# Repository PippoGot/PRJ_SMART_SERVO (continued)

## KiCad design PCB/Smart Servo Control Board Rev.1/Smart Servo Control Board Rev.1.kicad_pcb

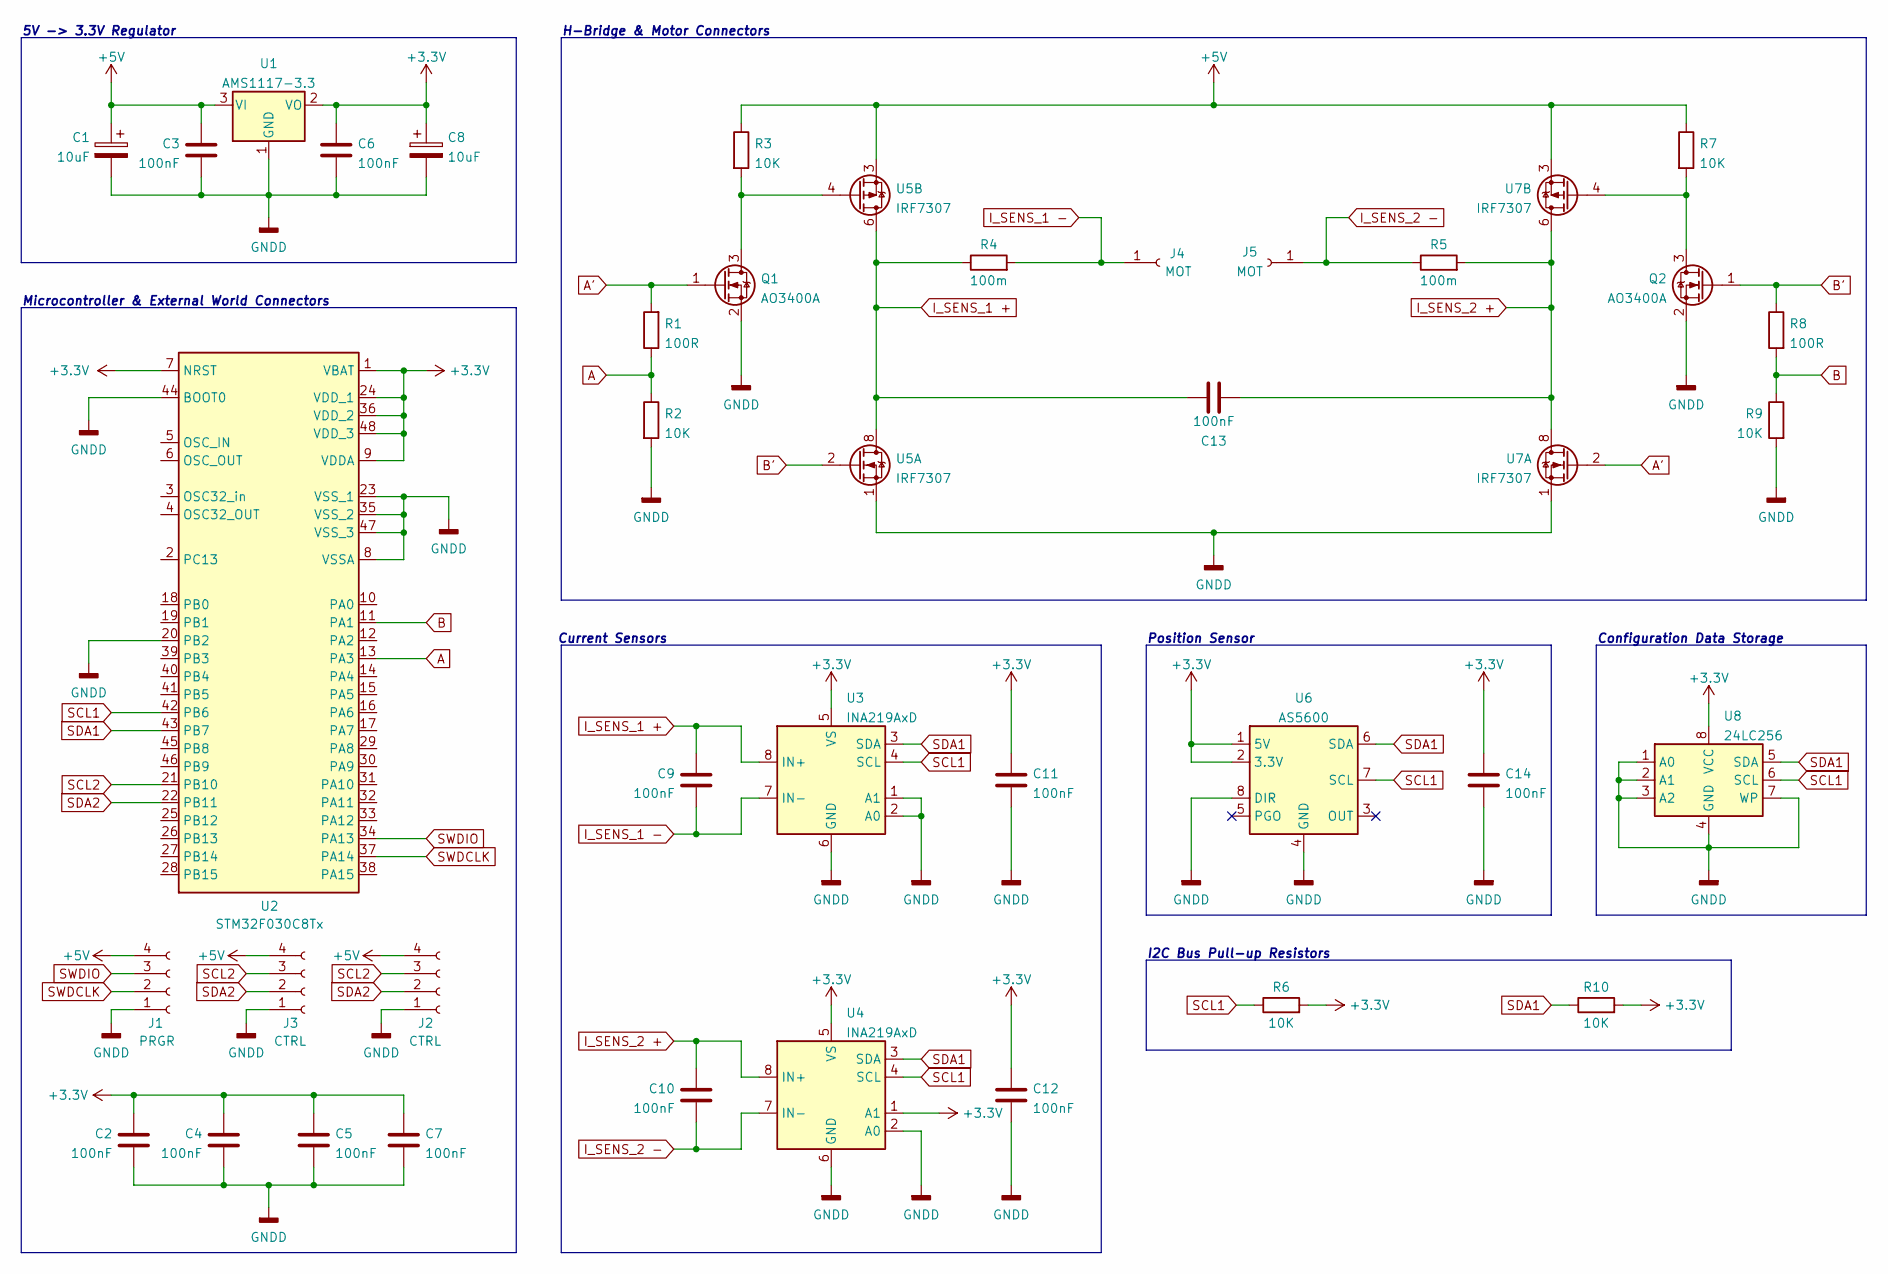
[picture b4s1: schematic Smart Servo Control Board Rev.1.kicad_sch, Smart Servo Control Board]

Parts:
C1, C8: 10uF; C_0603_1608Metric_Pad1.08x0.95mm_HandSolder
C2, C3, C4, C5, C6, C7, C9, C10, C11, C12, C13, C14: 100nF; C_0603_1608Metric_Pad1.08x0.95mm_HandSolder
J1: PRGR; PinSocket_1x04_P2.54mm_Vertical
J2, J3: CTRL; PinSocket_1x04_P2.54mm_Vertical
J4, J5: MOT; PinSocket_1x01_P2.54mm_Vertical
Q1, Q2: AO3400A; SOT-23
R1, R8: 100R; R_0603_1608Metric_Pad0.98x0.95mm_HandSolder
R2, R3, R6, R7, R9, R10: 10K; R_0603_1608Metric_Pad0.98x0.95mm_HandSolder
R4, R5: 100m; R_1206_3216Metric_Pad1.30x1.75mm_HandSolder
U1: AMS1117-3.3; SOT-223-3_TabPin2
U2: STM32F030C8Tx; LQFP-48_7x7mm_P0.5mm
U3, U4: INA219AxD; SOIC-8_3.9x4.9mm_P1.27mm
U5, U7: IRF7307; SOIC-8_3.9x4.9mm_P1.27mm
U6: AS5600; SOIC-8_3.9x4.9mm_P1.27mm
U8: 24LC256; SOIC-8_3.9x4.9mm_P1.27mm

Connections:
+3V3: C2.1, C4.1, C5.1, C6.1, C7.1, C8.1, C11.2, C12.2, C14.1, R6.2, R10.2, U1.2 (VO), U2.1 (VBAT), U2.7 (NRST), U2.9 (VDDA), U2.24 (VDD_1), U2.36 (VDD_2), U2.48 (VDD_3), U3.5 (VS), U4.1 (A1), U4.5 (VS), U6.1 (5V), U6.2 (3.3V), U8.8 (VCC)
+5V: C1.1, C3.1, J1.4, J2.4, J3.4, R3.1, R7.1, U1.3 (VI), U5.3, U7.3
A: R1.1, R2.1, U2.13 (PA3)
A': Q1.1 (G), R1.2, U7.2
B: R8.2, R9.1, U2.11 (PA1)
B': Q2.1 (G), R8.1, U5.2
GNDD: C1.2, C2.2, C3.2, C4.2, C5.2, C6.2, C7.2, C8.2, C11.1, C12.1, C14.2, J1.1, J2.1, J3.1, Q1.2 (S), Q2.2 (S), R2.2, R9.2, U1.1 (GND), U2.8 (VSSA), U2.20 (PB2), U2.23 (VSS_1), U2.35 (VSS_2), U2.44 (BOOT0), U2.47 (VSS_3), U3.1 (A1), U3.2 (A0), U3.6 (GND), U4.2 (A0), U4.6 (GND), U5.1, U6.4 (GND), U6.8 (DIR), U7.1, U8.1 (A0), U8.2 (A1), U8.3 (A2), U8.4 (GND), U8.7 (WP)
I_SENS_1 +: C9.1, C13.1, R4.1, U3.8 (IN+), U5.5, U5.6, U5.7, U5.8
I_SENS_1 -: C9.2, J4.1, R4.2, U3.7 (IN-)
I_SENS_2 +: C10.1, C13.2, R5.2, U4.8 (IN+), U7.5, U7.6, U7.7, U7.8
I_SENS_2 -: C10.2, J5.1, R5.1, U4.7 (IN-)
unnamed: Q1.3 (D), R3.2, U5.4
unnamed: Q2.3 (D), R7.2, U7.4
SCL1: R6.1, U2.42 (PB6), U3.4 (SCL), U4.4 (SCL), U6.7 (SCL), U8.6 (SCL)
SCL2: J2.3, J3.3, U2.21 (PB10)
SDA1: R10.1, U2.43 (PB7), U3.3 (SDA), U4.3 (SDA), U6.6 (SDA), U8.5 (SDA)
SDA2: J2.2, J3.2, U2.22 (PB11)
SWDCLK: J1.2, U2.37 (PA14)
SWDIO: J1.3, U2.34 (PA13)

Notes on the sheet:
Configuration Data Storage
Position Sensor
I2C Bus Pull-up Resistors
H-Bridge & Motor Connectors
5V -> 3.3V Regulator
Current Sensors
Microcontroller & External World Connectors

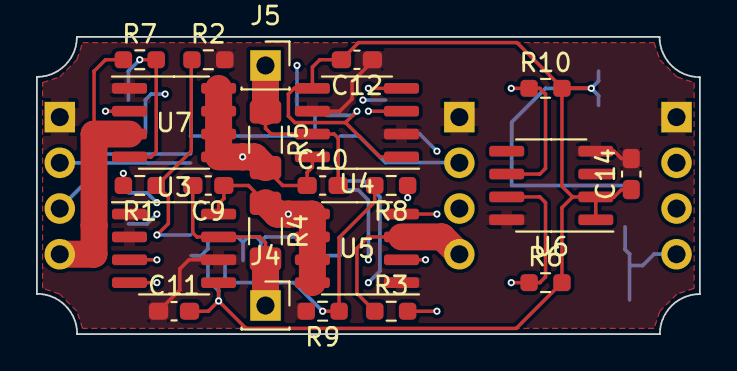
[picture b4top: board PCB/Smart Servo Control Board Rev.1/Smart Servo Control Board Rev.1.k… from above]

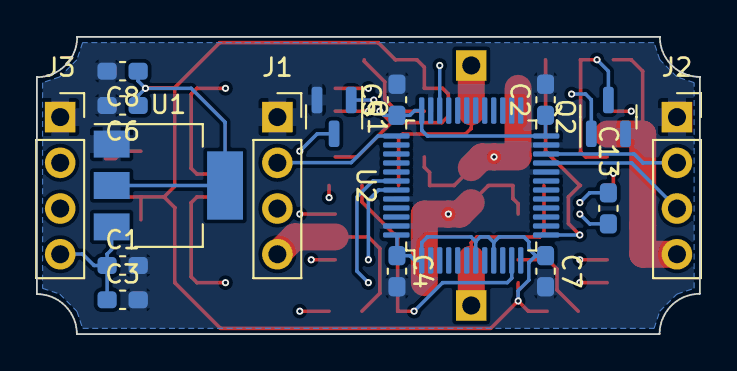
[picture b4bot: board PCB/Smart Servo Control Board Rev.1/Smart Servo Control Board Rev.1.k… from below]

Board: 4 copper layers, 36.8 x 16.5 mm, 38 parts (16 on the bottom side), 19 nets.

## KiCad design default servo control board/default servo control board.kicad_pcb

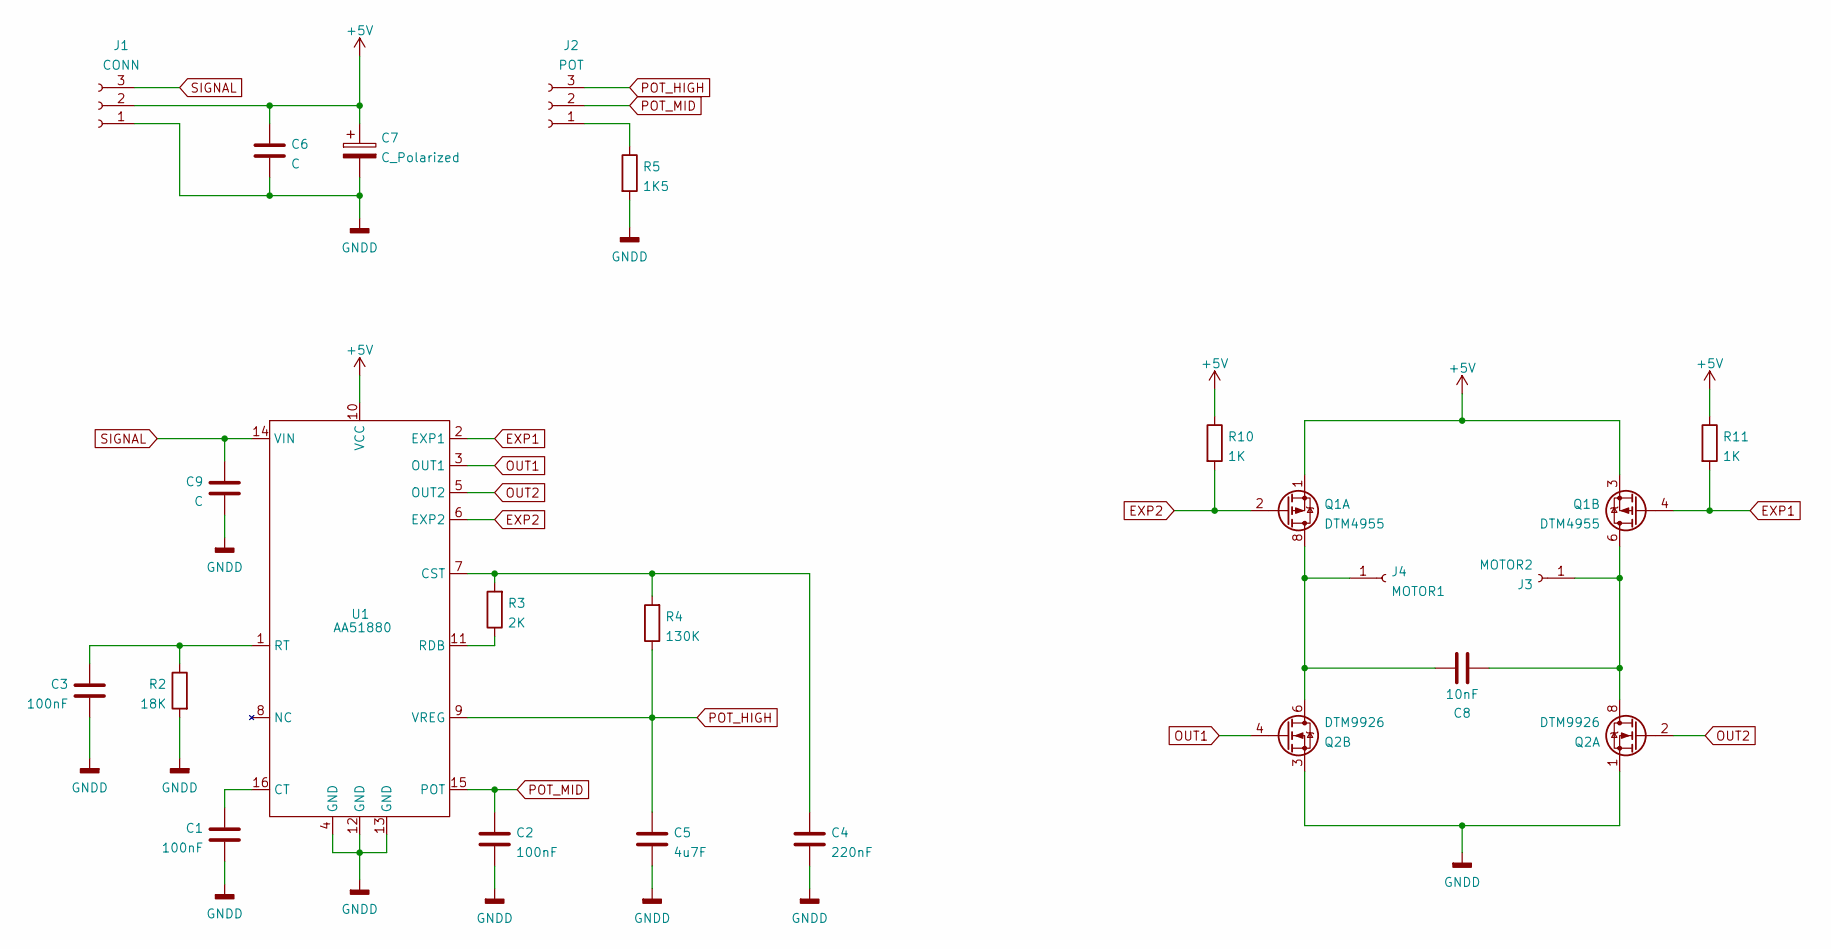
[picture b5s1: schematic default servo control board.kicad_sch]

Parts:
C1, C2, C3: 100nF; C_0402_1005Metric
C4: 220nF; C_0402_1005Metric
C5: 4u7F; C_0402_1005Metric
C6, C9: C; C_0402_1005Metric
C7: C_Polarized; C_1206_3216Metric
C8: 10nF; C_0402_1005Metric
J1: CONN; surface connector 1x3
J2: POT; PinSocket_1x03_P2.54mm_Vertical
J3: MOTOR2; PinSocket_1x01_P2.54mm_Vertical
J4: MOTOR1; PinSocket_1x01_P2.54mm_Vertical
Q1: DTM4955; SOIC-8_3.9x4.9mm_P1.27mm
Q2: DTM9926; SOIC-8_3.9x4.9mm_P1.27mm
R2: 18K; R_0402_1005Metric
R3: 2K; R_0402_1005Metric
R4: 130K; R_0402_1005Metric
R5: 1K5; R_0402_1005Metric
R10, R11: 1K; R_0402_1005Metric
U1: AA51880; SSOP-16_3.9x4.9mm_P0.635mm

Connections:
+5V: C6.1, C7.1, J1.2, Q1.1 (S1), Q1.3 (S2), R10.1, R11.1, U1.10 (VCC)
EXP1: Q1.4 (G2), R11.2, U1.2 (EXP1)
EXP2: Q1.2 (G1), R10.2, U1.6 (EXP2)
GNDD: C1.1, C2.2, C3.2, C4.2, C5.2, C6.2, C7.2, C9.2, J1.1, Q2.1 (S1), Q2.3 (S2), R2.2, R5.2, U1.4 (GND), U1.12 (GND), U1.13 (GND)
unnamed: C1.2, U1.16 (CT)
unnamed: C3.1, R2.1, U1.1 (RT)
unnamed: C4.1, R3.2, R4.2, U1.7 (CST)
unnamed: C8.1, J4.1, Q1.7 (D1), Q1.8 (D1), Q2.5 (D2), Q2.6 (D2)
unnamed: J2.1, R5.1
unnamed: C8.2, J3.1, Q1.5 (D2), Q1.6 (D2), Q2.7 (D1), Q2.8 (D1)
unnamed: R3.1, U1.11 (RDB)
OUT1: Q2.4 (G2), U1.3 (OUT1)
OUT2: Q2.2 (G1), U1.5 (OUT2)
POT_HIGH: C5.1, J2.3, R4.1, U1.9 (VREG)
POT_MID: C2.1, J2.2, U1.15 (POT)
SIGNAL: C9.1, J1.3, U1.14 (VIN)

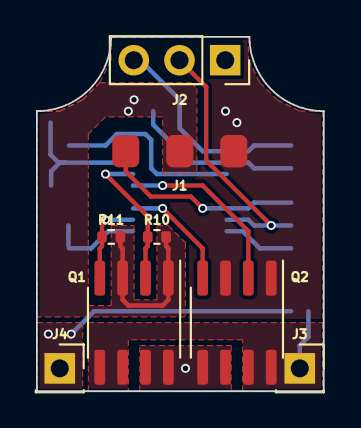
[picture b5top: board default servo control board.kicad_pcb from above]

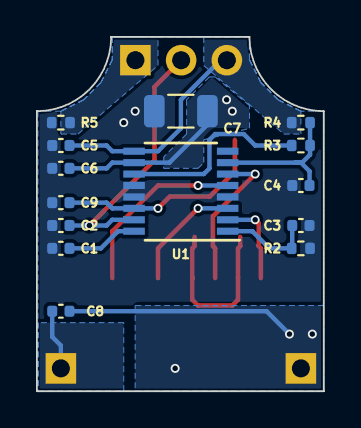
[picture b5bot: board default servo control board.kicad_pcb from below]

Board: 2 copper layers, 15.9 x 19.7 mm, 22 parts (14 on the bottom side), 16 nets.

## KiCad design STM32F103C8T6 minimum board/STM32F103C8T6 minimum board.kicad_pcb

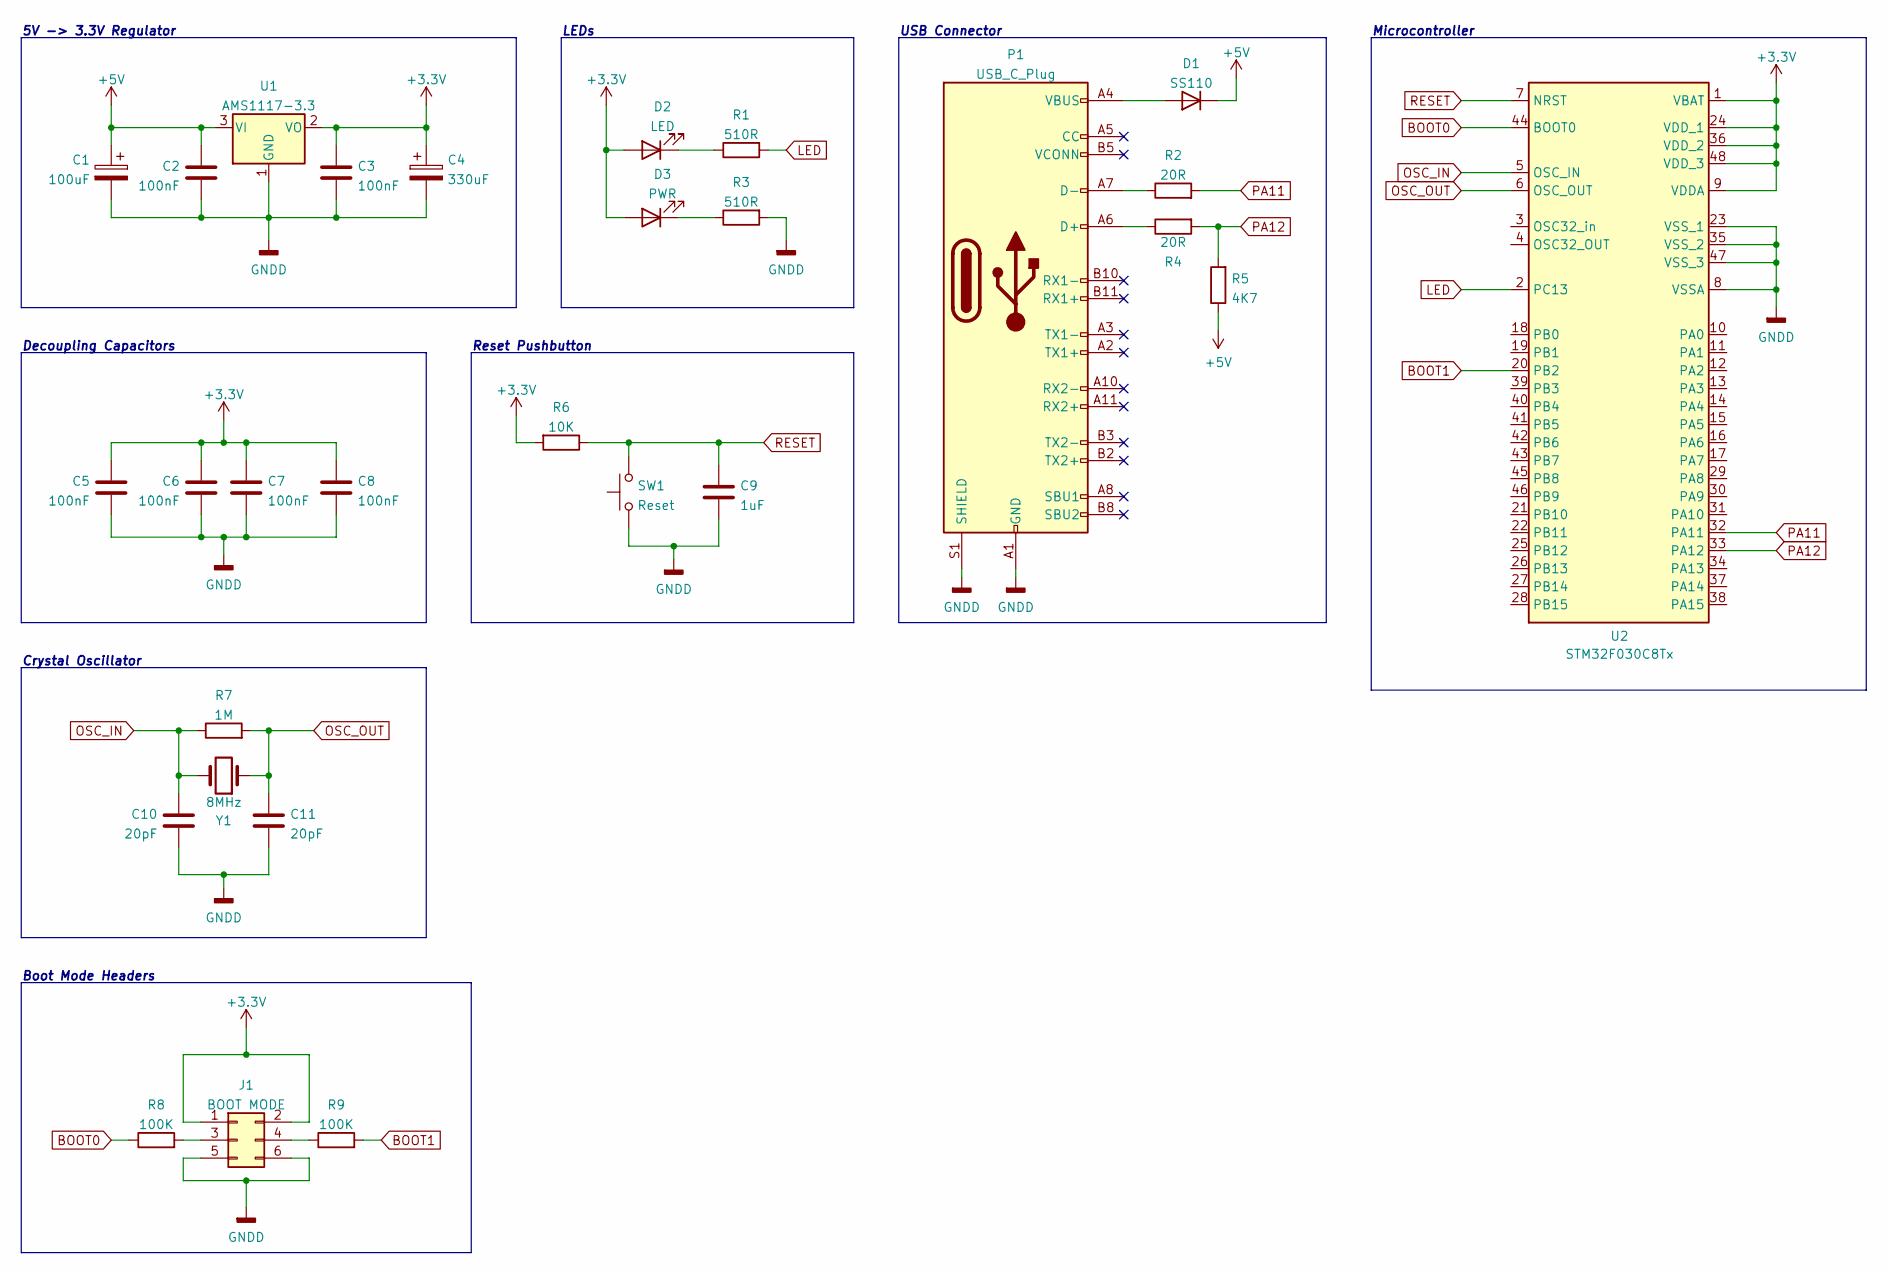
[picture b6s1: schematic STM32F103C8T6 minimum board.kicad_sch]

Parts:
C1: 100uF; C_0603_1608Metric
C2, C3, C5, C6, C7, C8: 100nF; C_0603_1608Metric
C4: 330uF; C_0603_1608Metric
C9: 1uF; C_0603_1608Metric
C10, C11: 20pF; C_0603_1608Metric
D1: SS110; D_SMA
D2: LED; D_0201_0603Metric
D3: PWR; D_0201_0603Metric
J1: BOOT MODE; PinHeader_2x03_P2.54mm_Vertical_SMD
P1: USB_C_Plug; USB_C_Receptacle_HRO_TYPE-C-31-M-12
R1, R3: 510R; R_0603_1608Metric
R2, R4: 20R; R_0603_1608Metric
R5: 4K7; R_0603_1608Metric
R6: 10K; R_0603_1608Metric
R7: 1M; R_0603_1608Metric
R8, R9: 100K; R_0603_1608Metric
SW1: Reset; SW_SPST_B3U-1000P
U1: AMS1117-3.3; SOT-223-3_TabPin2
U2: STM32F030C8Tx; LQFP-48_7x7mm_P0.5mm
Y1: 8MHz; Crystal_SMD_5032-2Pin_5.0x3.2mm

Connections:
+3V3: C3.1, C4.1, C5.1, C6.1, C7.1, C8.1, D2.2 (A), D3.2 (A), J1.1, J1.2, R6.2, U1.2 (VO), U2.1 (VBAT), U2.9 (VDDA), U2.24 (VDD_1), U2.36 (VDD_2), U2.48 (VDD_3)
+5V: C1.1, C2.1, D1.2 (K), R5.1, U1.3 (VI)
BOOT0: R8.1, U2.44 (BOOT0)
BOOT1: R9.2, U2.20 (PB2)
GNDD: C1.2, C2.2, C3.2, C4.2, C5.2, C6.2, C7.2, C8.2, C9.2, C10.2, C11.2, J1.5, J1.6, P1.A1 (GND), P1.A12 (GND), P1.B1 (GND), P1.B12 (GND), P1.S1 (SHIELD), R3.2, SW1.1, U1.1 (GND), U2.8 (VSSA), U2.23 (VSS_1), U2.35 (VSS_2), U2.47 (VSS_3)
LED: R1.2, U2.2 (PC13)
unnamed: D1.1 (A), P1.A4 (VBUS), P1.A9 (VBUS), P1.B4 (VBUS), P1.B9 (VBUS)
unnamed: D2.1 (K), R1.1
unnamed: D3.1 (K), R3.1
unnamed: J1.3, R8.2
unnamed: J1.4, R9.1
unnamed: P1.A6 (D+), R4.1
unnamed: P1.A7 (D-), R2.1
OSC_IN: C10.1, R7.1, U2.5 (OSC_IN), Y1.2
OSC_OUT: C11.1, R7.2, U2.6 (OSC_OUT), Y1.1
PA11: R2.2, U2.32 (PA11)
PA12: R4.2, R5.2, U2.33 (PA12)
RESET: C9.1, R6.1, SW1.2, U2.7 (NRST)

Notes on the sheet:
LEDs
USB Connector
Crystal Oscillator
Microcontroller
Decoupling Capacitors
Reset Pushbutton
Boot Mode Headers
5V -> 3.3V Regulator

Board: 2 copper layers, 29 parts (0 on the bottom side), 18 nets, no tracks yet.

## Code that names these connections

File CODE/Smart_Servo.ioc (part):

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Mcu.Name=STM32F103C(8-B)Tx
Mcu.Package=LQFP48
Mcu.UserName=STM32F103C8Tx
PA0-WKUP.Signal=S_TIM2_CH1_ETR
PA1.Signal=S_TIM2_CH2
PA13.Mode=Serial_Wire
PA13.Signal=SYS_JTMS-SWDIO
PA14.Mode=Serial_Wire
PA14.Signal=SYS_JTCK-SWCLK
PA2.Signal=ADCx_IN2
PA3.Signal=ADCx_IN3
PB10.Mode=I2C
PB10.Signal=I2C2_SCL
PB11.Mode=I2C
PB11.Signal=I2C2_SDA
PB6.Mode=I2C
PB6.Signal=I2C1_SCL
PB7.Mode=I2C
PB7.Signal=I2C1_SDA
RCC.SYSCLKFreq_VALUE=64000000
RCC.SYSCLKSource=RCC_SYSCLKSOURCE_PLLCLK
board=custom

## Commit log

2023-10-11 Initial push
    Push of the starting files
2023-10-11 Modello Simulink
    Creato modello simulink iniziale del motore e del ponte H.
    Sono da stimare/misurare i valori del motore e da fare refactoring del modello simulink per un migliore layout.
2023-10-13 piccoli cambiamenti al modello simulink
    Provato a vedere la corrente del carico totale e del motore in condizioni normali, a pieno carico e di shoot-through
    by PippoGot
2023-10-13 Sistemato il modello simulink
    ho sistemato e riordinato il modello simulink. ho sostituito il modello del ponte H fatto a transistor con un blocco apposito, probabilmente ci sono impostazioni sbagliate sui mosfet da sistemare.
2023-10-19 Aggiornamento gitignore
    aggiunti file automaticamente generati da matlab al gitignore
2023-10-19 Chiuso loop di controllo
    prima prova per l'anello di controllo, il controllore va progettato meglio, deve anche includere una soglia di errore nel quale non si attiva.
    risistemato il circuito del ponte H, non si possono rimuovere i MOSFET AO3400 a causa della differenza tra le tensioni di alimentazione del microcontrollore e del motore, però si può provare a usare 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
2023-10-23 Aggiunto file README
    Aggiunto file README per riassumere gli obiettivi del progetto e descrivere la struttura delle cartelle
2023-10-23 Aggiunti parametri e provato a progettare il controllore
    Il controllore da problemi e probabilmente è da riprogettare. Aggiunti i parametri del motore e dei MOSFET
2023-10-23 Aggiunta cartella per il codice
    creata la cartella in cui verrà messo tutto il codice per il microcontrollore
2023-10-23 Aggiunto file specifiche per il blocco PWM
    file per il comportamento del blocco PWM simulink
2023-10-23 Aggiunto file specifiche blocco PWM simulink
2023-10-23 Creato modello del motore su simulink
    nuovo modello simulink puro del motore per confronto.
    modifica unità di misura su params motor.J
2023-10-23 Rimossi file matlab generati automaticamente
2023-10-23 Risistemato il motore Simscape
2023-10-23 Aggiornato gitignore
2023-10-23 Rimossi file generati automaticamente da matlab
2023-10-23 Preparata scaletta per misure dei parametri
2023-10-23 cambiata estensione del file readme
2023-10-24 Testato collegamento simulink - ESP32
    riuscito il collegamento tra simulink e la scheda ESP32.
    aggiunti i file generati automaticamente da matlab al gitignore.
    rinominata la cartella per le simulazioni, gli spazi nel nome davano errore per il file si simulazione.
2023-10-24 Aggiunto file pinout per ESP32
2023-10-25 Creati simulink per stima parametri
    creati schemi simulink (da riempire con valori corretti) per stimare Kphi e B. Aggiunto anche un
2023-10-26 current and speed controller matlab code
    Added file DS_Store on gitignore
2023-10-27 Provare blocco implementato da Pippo
2023-10-27 controllori
    Abbiamo cercato di risolvere overshoot di velocità e corrente - scarsi risultati
2023-10-29 Rinominata cartella "MODELS & SIMULATIONS"
2023-10-29 Implementato pwm controller da pippo
2023-10-30 Controllore velocità
    Probabilmente il controllore per la velocità è stato calcolato bene, incluso anche il loop di corrente.
    cominciato il loop per la posizione
2023-10-31 Controllore sistemato
    il codice per i parametri del controllore funzionano, anche se rimane da capire come calcolare il Kp della posizione. risistemare blocchi controllore prima di fare merge
2023-11-01 Implementato il controllore
    il controllore è completo e funzionante
2023-11-01 Connessi tutti i blocchi utili
    collegati controllore, interfaccia PWM, ponte H e motore assieme e testato il modello. funziona
2023-11-03 Current sensor - iniziato
    Aggiornato valori resistenza e induttanza
2023-11-06 sensore corrente e discretizzazione
    non funziona bene in discreto
2023-11-08 pwm functions
2023-11-08 Creato progetto stm32
    creato il file e la cartella di progetto stm32.
    testato il pwm con successo
2023-11-08 Risistemato codice parametri e modello simulink
    risistemato il modello simulink e il codice dei parametri.
    la simulazione è lenta e il funzionamento del controllore è da verificare.
2023-11-09 Creation of matlab and simulink file for the estimetion of paramiters
    Creation of matlab file for the estimetion of paramiters.
    Creation of simulink file, with the interface for arduino, for the two esperiments needed for the estimetion of paramiters.
2023-11-10 Cambiato blocco PWM
    ora la simulazione funziona in modo corretto. provare diversi tempi di campionamento e frequenze pwm, e aggiungere rumore.
2023-11-11 Aggiunto sensore di posizione
    quando il sistema arriva vicino alla reference oscilla in modo divergente, da sistemare, provare con il kalman filter
2023-11-13 Creato sketch di test per l'encoder in ESP32 con arduino ide
2023-11-13 Rimosso modello motore simulink
2023-11-14 Testato sistema per acquisizione dei parametri
    testato con successo lo schema simulink per il collegamento con la scheda ESP32, l'acquisizione dei dati e il comando del PWM (al momento usato solo al massimo del duty cycle e non a valori intermedi)
2023-11-17 Implementate moduli e classi per interfaccia I2C
    implementato generica classe per la comunicazione via I2C.
    implementata sottoclasse per il sensore AS5600.
    compila ok, testate alcune funzioni, va testato completamente e documentato il codice in dettaglio.
2023-11-20 Codice per acquisizione dati caratteristica servo vecchio
2023-11-20 Kalman problems!!!
2023-11-21 Kalman simulink
2023-11-21 lieve modifica alle conversioni di misura
    ancora non funziona correttamente, problema di stima della posizione
2023-11-22 iniziato board design
2023-11-22 salvataggio layout board
    tornare a questo salvataggio per riprovare.
    piani potenza interni e piani segnali esterni, da scambiare ?
2023-11-25 implementata libreria per sensore INA219
    implementata libreria per INA219.
    piccolo refactoring della libreria per AS5600 e I2C device.
    semplice test della lettura di corrente con esito positivo.
    rimane da documentare l'intero codice scritto.
    possibile modifica della libreria per implementare il sensore anche come sensore di tensione ?
2023-11-28 Acquisiti dati caratteristica servo
    acquisiti dati per la verifica del (mal)funzionamento dell'output del servomotore e tracciati grafici di caratteristica, errore e isteresi.
2023-11-28 Aggiunte misure di un secondo servo
2023-11-28 Test CubeMonitor
    testata app per l'acqusizione e visualizzazione di dati da scheda STM32
2023-11-29 commentato modulo per INA219
    commentato tutto il modulo scritto per il sensore di corrente INA219
2023-11-30 Aggiunto file simulink per la simulazione della stima di J
    Aggiunto file simulink per la simulazione della stima di J
2023-11-30 File aggiornato con interfaccia I2C
    File aggiornato con interfaccia I2C
2023-11-30 Implementato observer con successo
    tuttavia quando viene usato per il feedback, una volta arrivato a regime il sistema oscilla troppo
2023-11-30 Eliminati file inutilizzati
2023-11-30 Implementato kalman filter
    sembra funzionare a meno di una stima parametri del motore.
    da provare ad aggiungere il rumore e discretizzare tutto.
2023-12-01 commentato modulo per AS5600
    commentato tutto il modulo scritto per il sensore AS5600.
    leggere modifiche anche alla documentazione del modulo INA219.
2023-12-01 commentato modulo I2C Device
2023-12-01 iniziato a implementare funzioni per INA219 come sensore di tensione
    scritte funzioni per il snesing di corrente con INA219.
    asimmetria della tensione letta col sensore, in particolare, la tensione va a circa -5V girando in un verso, mentre a +7.5 volt girando nell'altro (sbagliato).
2023-12-02 rimosse modifiche per INA219 come sensore di tensione
    il sensore viene impiegato in modo diverso per misurare la tensione ai capi del carico. in particolare ne vengono utilizzati 2 in antiserie per misurare una corrente opposta e una tensione di bus opp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
2023-12-04 Prima versione definitiva PCB
    tracciate le piste nel modo migliore possibile per ora, resta da sistemare il silkscreen.
2023-12-06 test per il logging delle misure per la stima dei parametri
    eseguito un test di logging per le misure delle grandezze di interesse. facile acquisizione e manipolazione tramite excel. da vedere compatibilità con matlab.
2023-12-06 sistemai riferimenti in PCB
2023-12-06 Acquisiti dati per la stima dei parametri
    acquisiti dati di tensione, corrente e posizione in gradi con input a scala e a triangolo.
    potrebbe essere necessario un filtro passabasso per corrente e tensione a causa del pwm.
    per la velocità angolare integrare la posizione.
2023-12-08 Aggiunto codice per importare dati da file e correzioni varie al codice
    Aggiunto codice per importare dati da file.
    Separazione dei due esperimenti.
    Correzioni varie al codice.
    Creati i grafici per visualizzare i dati.
2023-12-09 Aggiunti datasheet componenti e aggiunta EEPROM
    aggiunto chip EEPROMi2c e datasheet per INA219 e 24LC256.
2023-12-15 Discretization of the controller and observer
2023-12-15 discrete no funziona!
2023-12-26 aggiornamento per simulink di acquisizione dati
    tensione letta correttamente, corrente e velocità da controllare. progettare meglio filtri passabasso.
2024-01-04 creati primi file per modello modulare
    problema al controllore, si tenta un merge dove il controllore funzionava
2024-01-05 creati file modulari
2024-01-12 aggiunti file modello modulare
    e rivisto il controller tune
2024-01-12 modiffiche per misura velocità
2024-01-12 Tuning of the speed controller
2024-01-12 Gains changed
2024-01-12 risolto problema del controllo velocità
    ora i controllori di velocità e posizione funzionano correttamente.
    rimossi file inutili o obsoleti.
    preparato il modello per l'acquisizione parametri.
2024-01-12 perfezionato modello per acquisizione dati
2024-01-15 Test per acquisizione dati
    preparati i file per l'acquisizione dei dati ed eseguiti test con successo. risistemati tutti i file finora creati in modo modulare.
2024-01-16 acquisizione dati
2024-01-16 Creazione file 'Estimation_params_simulation.m'
    Creazione file per la verifica delle stime dei parametri tramite simulazione simulink
2024-01-18 Correzione stime simulazione
    Correzione stime simulazione e aggiunti due file ".mat" con i dati delle simulazioni dei due esperimenti
2024-01-18 Correzione errori file "Estimation_params.m"
    Correzione errori file "Estimation_params.m" ed adattamento per il calcolo delle stime con i file.mat dei dati degli esperimenti reali
2024-01-19 aggiunti i parametri stimati e iniziato il vero tuning del controllore
2024-01-19 LQR implementation
    Non funziona, esplode sempre. Ho provato a fare anche extended state space per fare un controllore robust ma è stato un fallimento.
2024-01-19 sistemati file per tuning del controllore
2024-02-09 Riordinati i file "Estimation_params.m" e "Estimation_params_simulation.m"
    Fatta pulizia e ordine nei due file
2024-02-14 presentazione
2024-02-14 tolta
2024-02-16 problema scoperto: nonlinear friction
2024-02-16 Auto stash before merge of "simulations" and "origin/simulations"
2024-02-16 Diagram Block skin
2024-02-20 Aggiunto dataset e bozza codice per la stima della curva di sribeck
2024-02-22 photos of the motor
2024-02-22 da sistemare
2024-02-22 photos jpeg
2024-02-22 prima versione presentazione
    da aggiungere video e foto gradini
2024-12-03 Updated with new simulink model, moved legacy material
2024-12-10 hardware in loop model and rebase of git repo
2024-12-10 !!GitHub_Desktop<simulations>
2024-12-11 progressi con il modello hardware in loop e misure rumore
2025-03-04 lugre model and LQR controller, compensation looks like could work
2025-04-13 Lugre and various tests
2025-04-13 modified hall sensor
2025-09-19 codice e scheda a buon punto
2025-10-01 incontro prof
2026-03-15 thesis update
